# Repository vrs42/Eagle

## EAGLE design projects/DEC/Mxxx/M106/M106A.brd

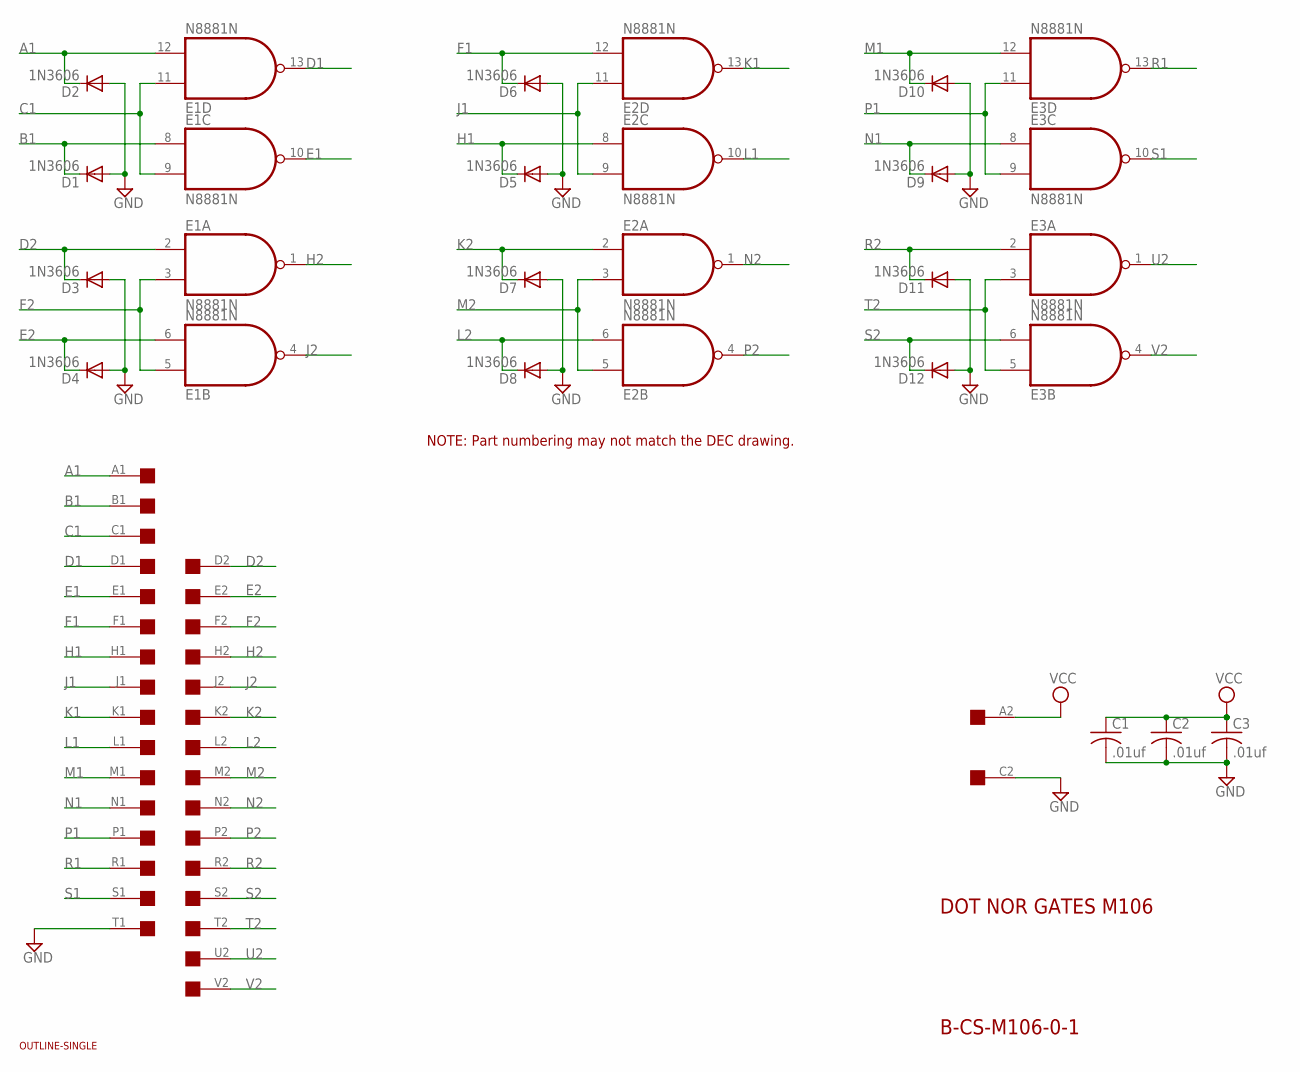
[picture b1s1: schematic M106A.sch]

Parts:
C1, C2, C3: .01uf; C050-025X075
D1, D2, D3, D4, D5, D6, D7, D8, D9, D10, D11, D12: 1N3606; DO35-10
E1, E2, E3: N8881N; DIL14
U$1: SINGLE; EDGE-CON2
U$4: OUTLINE-SINGLE; SINGLE

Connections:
A1: D2.C, E1.12 (I1), U$1.A1
B1: D1.C, E1.8 (I0), U$1.B1
C1: E1.9 (I1), E1.11 (I0), U$1.C1
D1: E1.13 (O), U$1.D1
D2: D3.C, E1.2 (I0), U$1.D2
E1: E1.10 (O), U$1.E1
E2: D4.C, E1.6 (I1), U$1.E2
F1: D6.C, E2.12 (I1), U$1.F1
F2: E1.3 (I1), E1.5 (I0), U$1.F2
GND: C1.2, C2.2, C3.2, D1.A, D2.A, D3.A, D4.A, D5.A, D6.A, D7.A, D8.A, D9.A, D10.A, D11.A, D12.A, E1.7 (GND), E2.7 (GND), E3.7 (GND), U$1.C2, U$1.T1
H1: D5.C, E2.8 (I0), U$1.H1
H2: E1.1 (O), U$1.H2
J1: E2.9 (I1), E2.11 (I0), U$1.J1
J2: E1.4 (O), U$1.J2
K1: E2.13 (O), U$1.K1
K2: D7.C, E2.2 (I0), U$1.K2
L1: E2.10 (O), U$1.L1
L2: D8.C, E2.6 (I1), U$1.L2
M1: D10.C, E3.12 (I1), U$1.M1
M2: E2.3 (I1), E2.5 (I0), U$1.M2
N1: D9.C, E3.8 (I0), U$1.N1
N2: E2.1 (O), U$1.N2
P1: E3.9 (I1), E3.11 (I0), U$1.P1
P2: E2.4 (O), U$1.P2
R1: E3.13 (O), U$1.R1
R2: D11.C, E3.2 (I0), U$1.R2
S1: E3.10 (O), U$1.S1
S2: D12.C, E3.6 (I1), U$1.S2
T2: E3.3 (I1), E3.5 (I0), U$1.T2
U2: E3.1 (O), U$1.U2
V2: E3.4 (O), U$1.V2
VCC: C1.1, C2.1, C3.1, E1.14 (VCC), E2.14 (VCC), E3.14 (VCC), U$1.A2

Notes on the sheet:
DOT NOR GATES M106
B-CS-M106-0-1
NOTE: Part numbering may not match the DEC drawing.

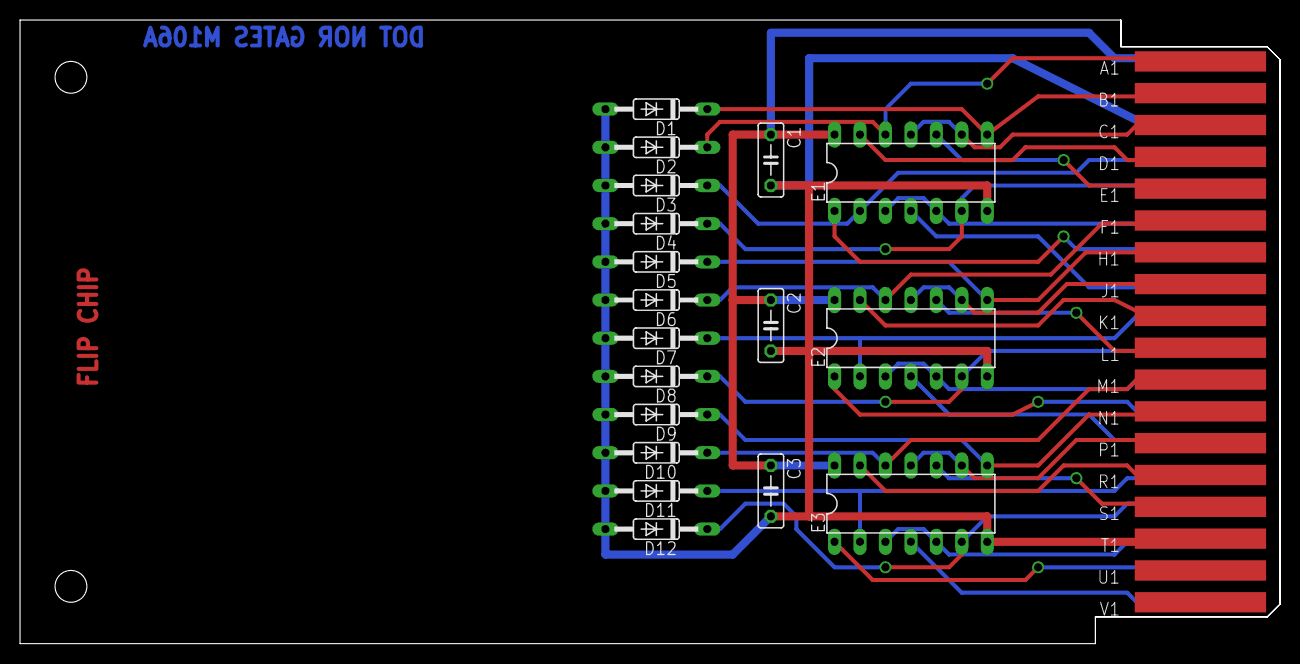
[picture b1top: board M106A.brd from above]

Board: 2 copper layers, 125.7 x 62.2 mm, 20 parts (0 on the bottom side), 32 nets.

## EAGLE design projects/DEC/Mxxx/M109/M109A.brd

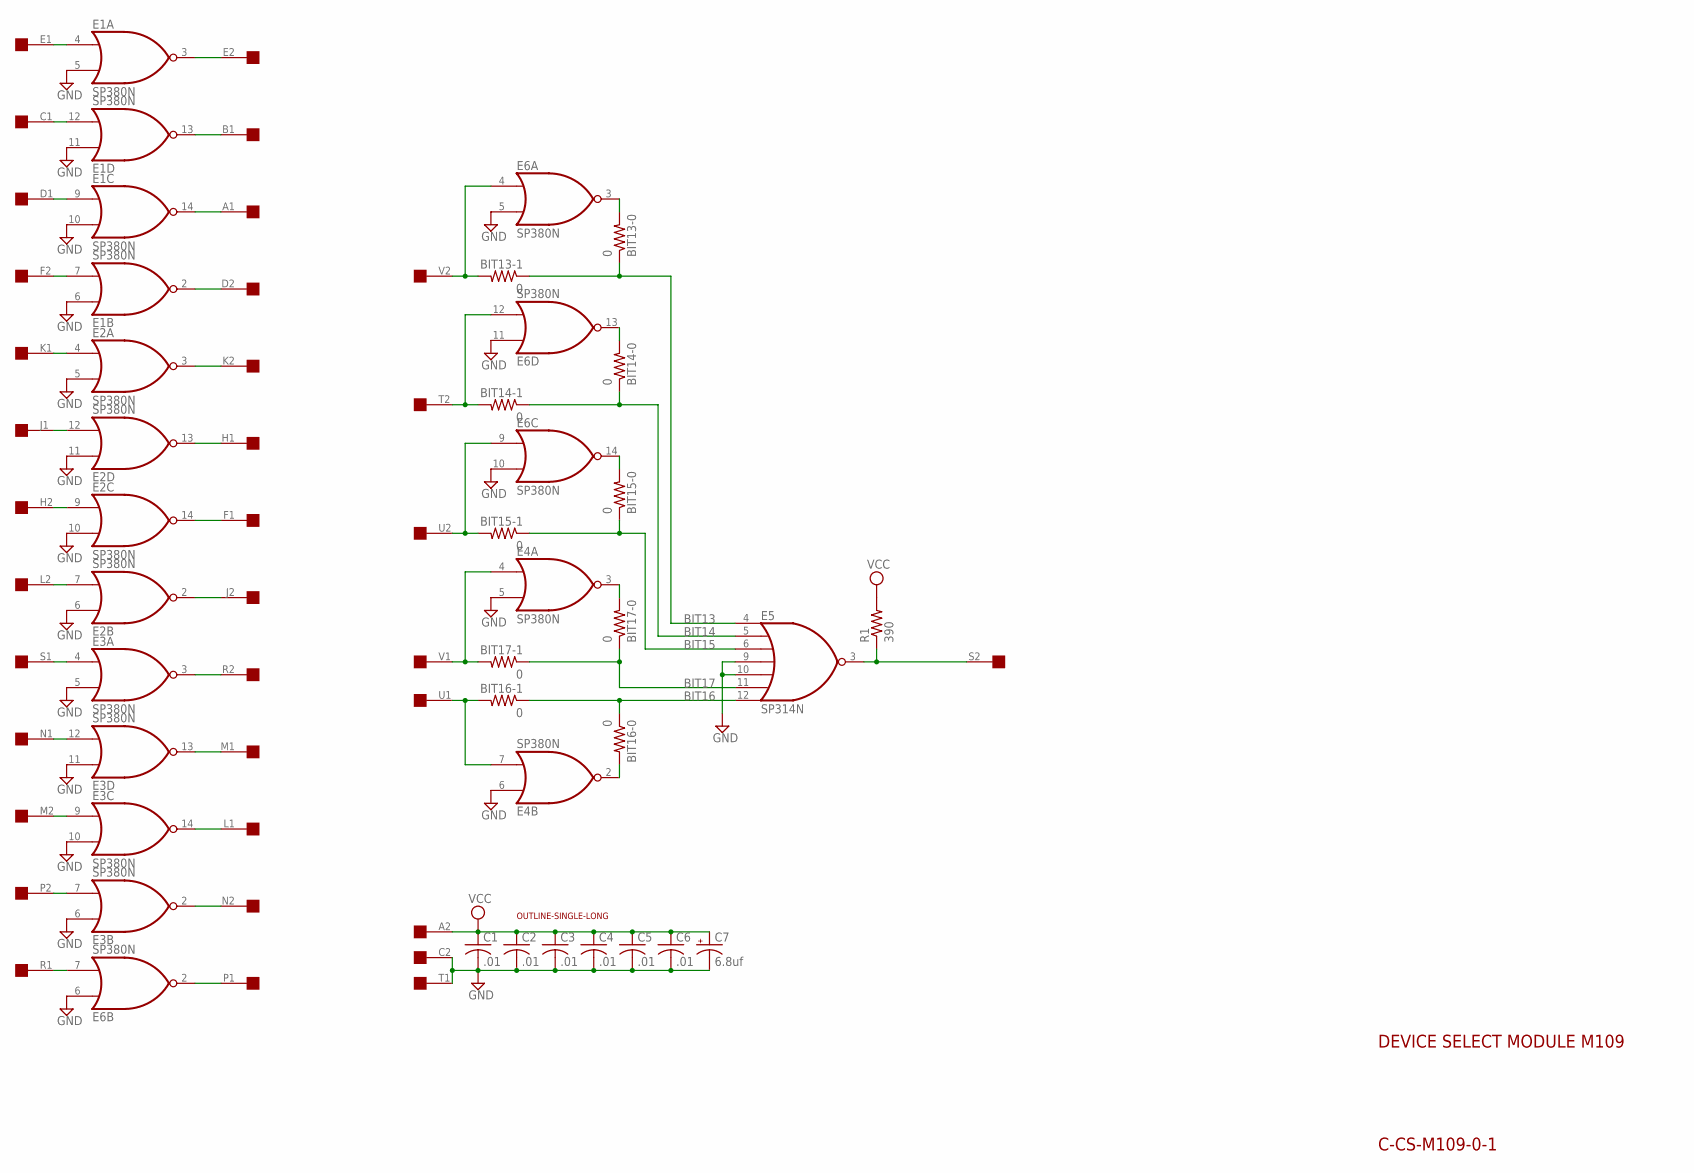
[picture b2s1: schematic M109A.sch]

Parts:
BIT13-0, BIT13-1, BIT14-0, BIT14-1, BIT15-0, BIT15-1, BIT16-0, BIT16-1, BIT17-0, BIT17-1: 0; 0207/10
C1, C2, C3, C4, C5, C6: .01; C050-025X075
C7: 6.8uf; E22-6
E1, E2, E3, E4, E6: SP380N; DIL14
E5: SP314N; DIL14
R1: 390; 0207/10
U$1: SINGLE; EDGE-CON2
U$2: OUTLINE-SINGLE-LONG; SINGLE-LONG

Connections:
BIT13: BIT13-0.1, BIT13-1.1, E5.4 (I0)
BIT14: BIT14-0.1, BIT14-1.1, E5.5 (I1)
BIT15: BIT15-0.1, BIT15-1.1, E5.6 (I2)
BIT16: BIT16-0.1, BIT16-1.1, E5.12 (I6)
BIT17: BIT17-0.1, BIT17-1.1, E5.11 (I5)
GND: C1.2, C2.2, C3.2, C4.2, C5.2, C6.2, C7.-, E1.1 (GND), E1.5 (I1), E1.6 (I0), E1.10 (I1), E1.11 (I0), E2.1 (GND), E2.5 (I1), E2.6 (I0), E2.10 (I1), E2.11 (I0), E3.1 (GND), E3.5 (I1), E3.6 (I0), E3.10 (I1), E3.11 (I0), E4.1 (GND), E4.5 (I1), E4.6 (I0), E5.1 (GND), E5.9 (I3), E5.10 (I4), E6.1 (GND), E6.5 (I1), E6.6 (I0), E6.10 (I1), E6.11 (I0), U$1.C2, U$1.T1
unnamed: E1.4 (I0), U$1.E1
unnamed: E2.12 (I1), U$1.J1
unnamed: E1.3 (O), U$1.E2
unnamed: E1.2 (O), U$1.D2
unnamed: E2.9 (I0), U$1.H2
unnamed: E2.3 (O), U$1.K2
unnamed: E2.13 (O), U$1.H1
unnamed: E3.13 (O), U$1.M1
unnamed: BIT15-0.2, E6.14 (O)
unnamed: E3.7 (I1), U$1.P2
unnamed: E6.7 (I1), U$1.R1
unnamed: E3.2 (O), U$1.N2
unnamed: BIT17-1.2, E4.4 (I0), U$1.V1
unnamed: BIT14-1.2, E6.12 (I1), U$1.T2
unnamed: BIT15-1.2, E6.9 (I0), U$1.U2
unnamed: E6.2 (O), U$1.P1
unnamed: E1.12 (I1), U$1.C1
unnamed: E1.7 (I1), U$1.F2
unnamed: E1.9 (I0), U$1.D1
unnamed: BIT14-0.2, E6.13 (O)
unnamed: BIT17-0.2, E4.3 (O)
unnamed: E1.14 (O), U$1.A1
unnamed: E1.13 (O), U$1.B1
unnamed: E2.14 (O), U$1.F1
unnamed: E2.2 (O), U$1.J2
unnamed: E2.7 (I1), U$1.L2
unnamed: E2.4 (I0), U$1.K1
unnamed: E3.14 (O), U$1.L1
unnamed: E3.12 (I1), U$1.N1
unnamed: E3.9 (I0), U$1.M2
unnamed: BIT16-1.2, E4.7 (I1), U$1.U1
unnamed: E3.3 (O), U$1.R2
unnamed: BIT16-0.2, E4.2 (O)
unnamed: BIT13-1.2, E6.4 (I0), U$1.V2
unnamed: BIT13-0.2, E6.3 (O)
unnamed: E5.3 (O), R1.1, U$1.S2
unnamed: E3.4 (I0), U$1.S1
VCC: C1.1, C2.1, C3.1, C4.1, C5.1, C6.1, C7.+, E1.8 (VCC), E2.8 (VCC), E3.8 (VCC), E4.8 (VCC), E5.8 (VCC), E6.8 (VCC), R1.2, U$1.A2

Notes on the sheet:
DEVICE SELECT MODULE M109
C-CS-M109-0-1

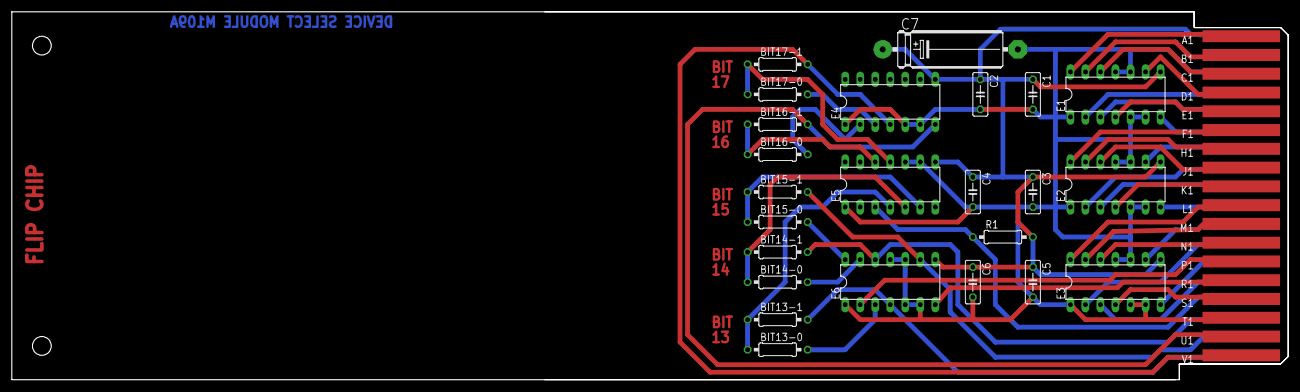
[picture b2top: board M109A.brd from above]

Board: 2 copper layers, 215.9 x 62.2 mm, 27 parts (0 on the bottom side), 44 nets.

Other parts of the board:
U$3: FLIPCHIP

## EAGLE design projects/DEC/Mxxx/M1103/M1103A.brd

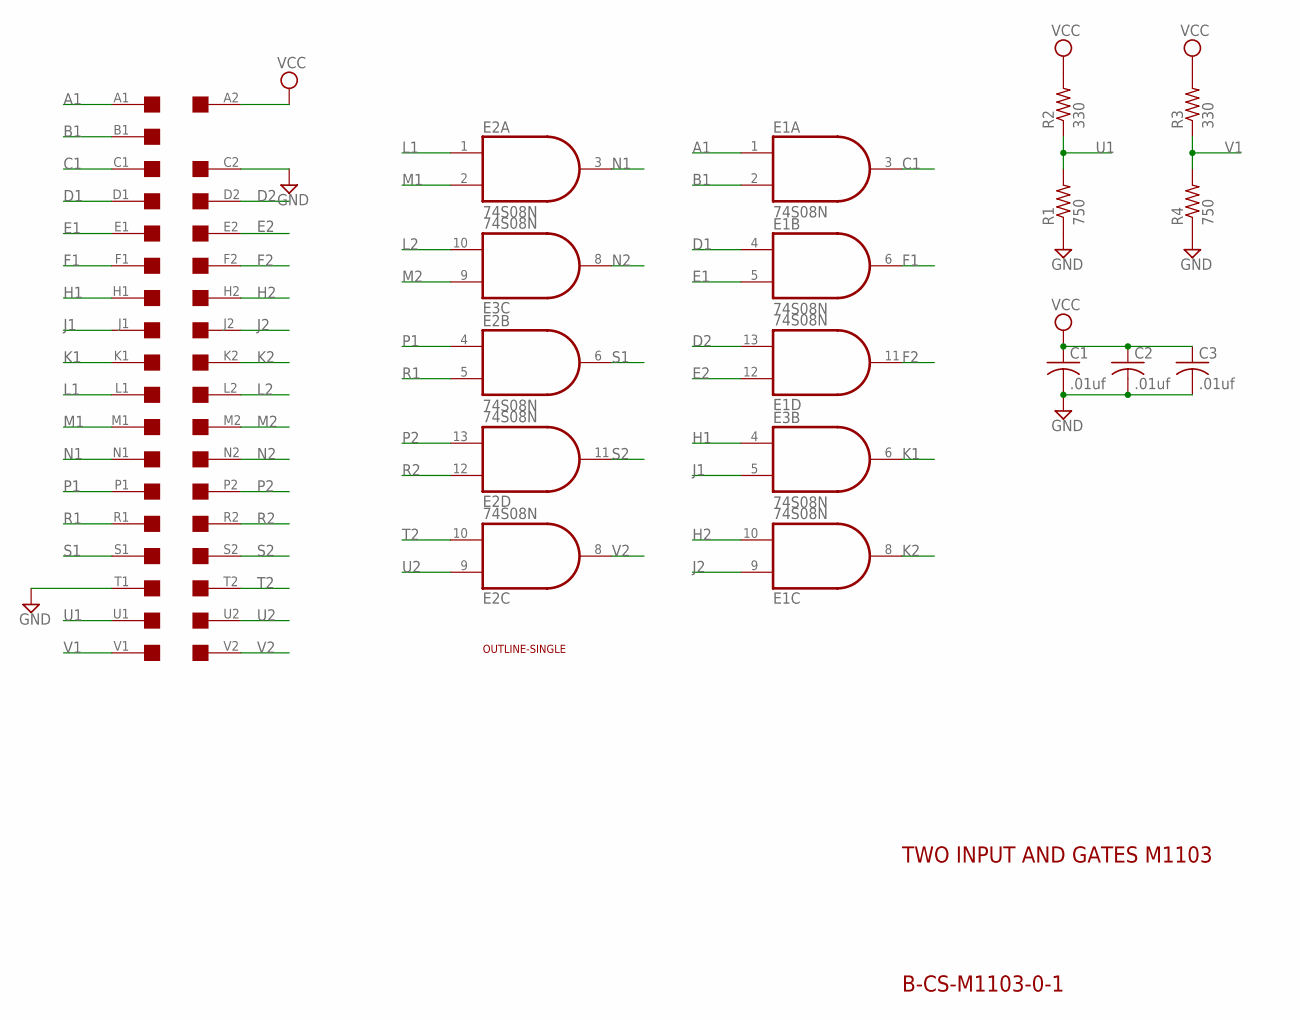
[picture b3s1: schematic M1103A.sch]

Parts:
C1, C2, C3: .01uf; C050-025X075
E1, E2, E3: 74S08N; DIL14
R1, R4: 750; 0207/10
R2, R3: 330; 0207/10
U$1: SINGLE; EDGE-CON2
U$2: OUTLINE-SINGLE; SINGLE

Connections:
A1: E1.1 (I0), U$1.A1
B1: E1.2 (I1), U$1.B1
C1: E1.3 (O), U$1.C1
D1: E1.4 (I0), U$1.D1
D2: E1.13 (I1), U$1.D2
E1: E1.5 (I1), U$1.E1
E2: E1.12 (I0), U$1.E2
F1: E1.6 (O), U$1.F1
F2: E1.11 (O), U$1.F2
GND: C1.2, C2.2, C3.2, E1.7 (GND), E2.7 (GND), E3.7 (GND), R1.1, R4.1, U$1.C2, U$1.T1
H1: E3.4 (I0), U$1.H1
H2: E1.10 (I1), U$1.H2
J1: E3.5 (I1), U$1.J1
J2: E1.9 (I0), U$1.J2
K1: E3.6 (O), U$1.K1
K2: E1.8 (O), U$1.K2
L1: E2.1 (I0), U$1.L1
L2: E3.10 (I1), U$1.L2
M1: E2.2 (I1), U$1.M1
M2: E3.9 (I0), U$1.M2
N1: E2.3 (O), U$1.N1
N2: E3.8 (O), U$1.N2
P1: E2.4 (I0), U$1.P1
P2: E2.13 (I1), U$1.P2
R1: E2.5 (I1), U$1.R1
R2: E2.12 (I0), U$1.R2
S1: E2.6 (O), U$1.S1
S2: E2.11 (O), U$1.S2
T2: E2.10 (I1), U$1.T2
U1: R1.2, R2.1, U$1.U1
U2: E2.9 (I0), U$1.U2
V1: R3.1, R4.2, U$1.V1
V2: E2.8 (O), U$1.V2
VCC: C1.1, C2.1, C3.1, E1.14 (VCC), E2.14 (VCC), E3.14 (VCC), R2.2, R3.2, U$1.A2

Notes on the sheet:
TWO INPUT AND GATES M1103
B-CS-M1103-0-1

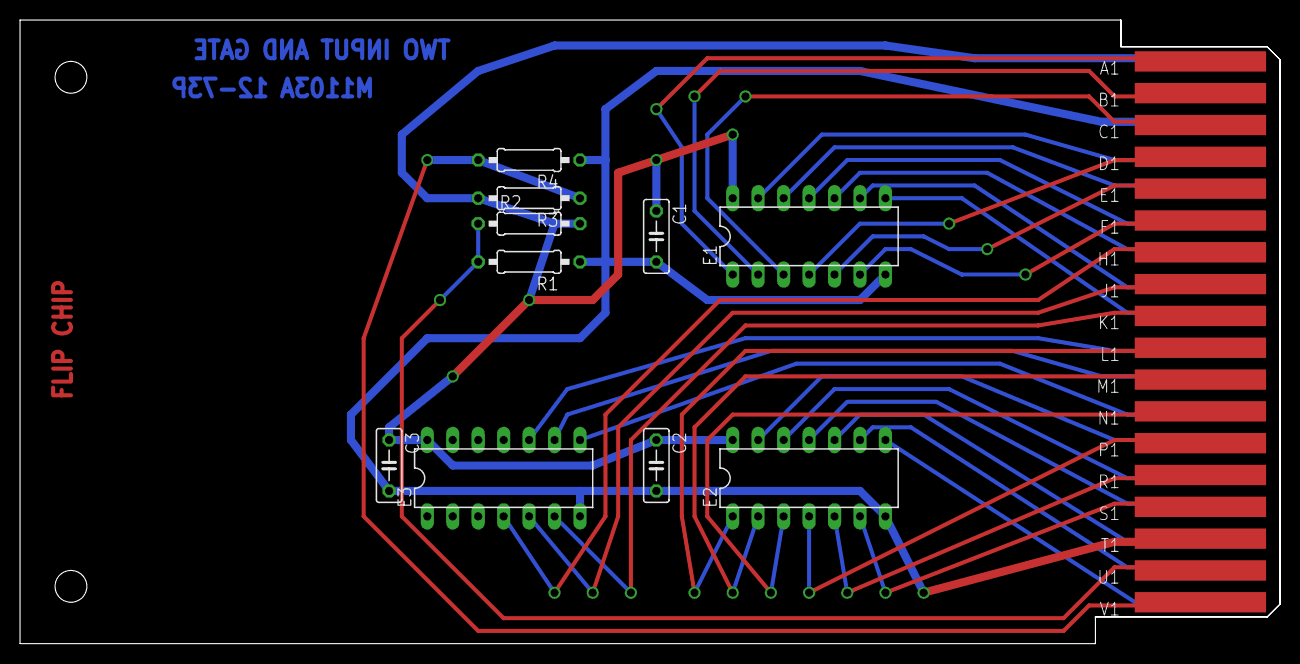
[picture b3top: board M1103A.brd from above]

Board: 2 copper layers, 125.7 x 62.2 mm, 12 parts (0 on the bottom side), 34 nets.

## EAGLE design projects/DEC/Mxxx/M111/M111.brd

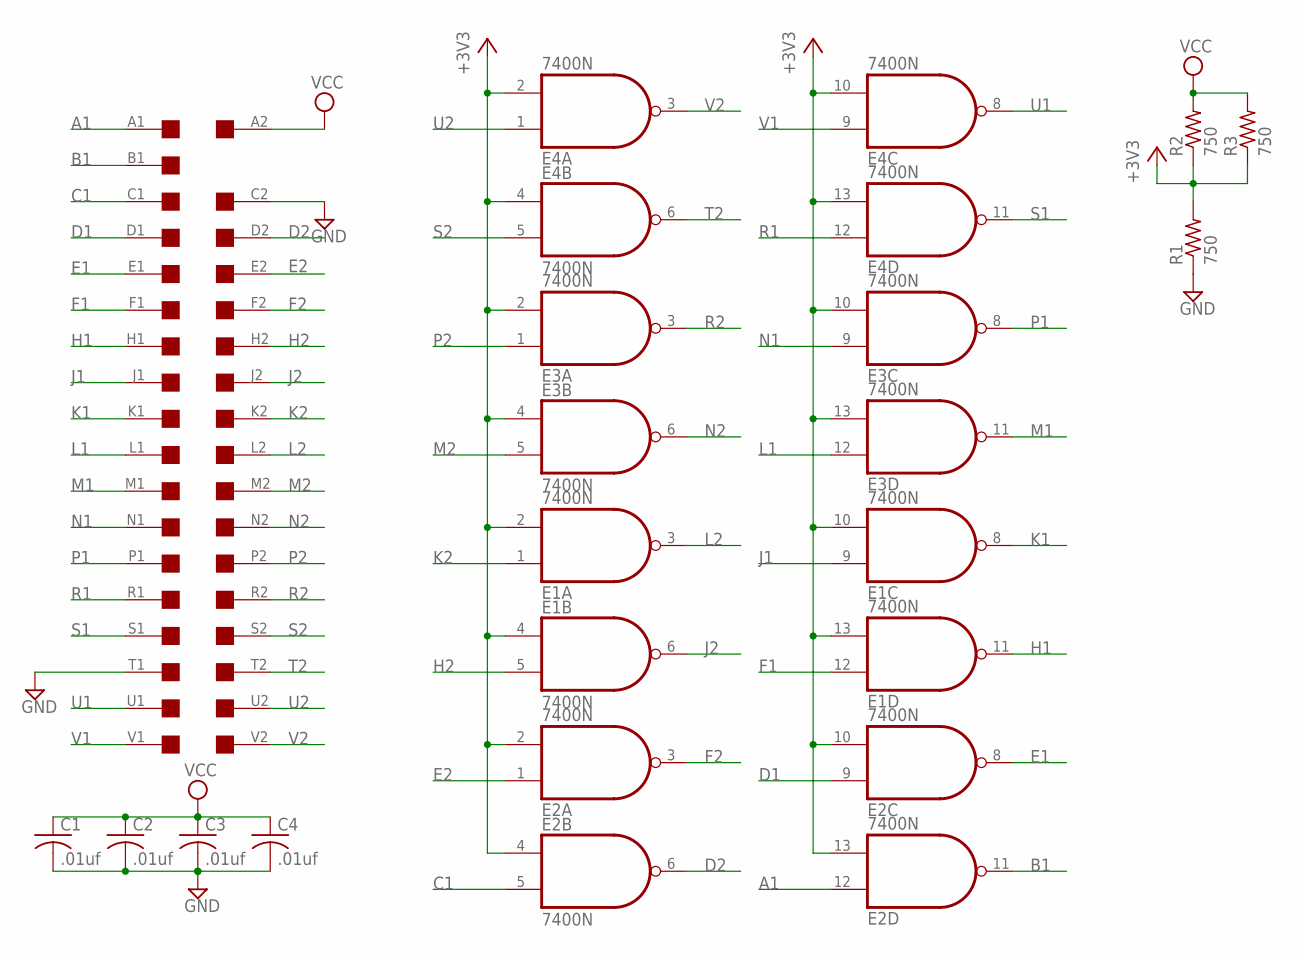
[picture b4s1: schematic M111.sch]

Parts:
A: EDGE-2CONNECTOR; EDGE-CON2
C1, C2, C3, C4: .01uf; C050-025X075
E1, E2, E3, E4: 7400N; DIL14
R1, R2, R3: 750; 0207/10

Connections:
+3V3: E1.2 (I1), E1.4 (I0), E1.10 (I1), E1.13 (I1), E2.2 (I1), E2.4 (I0), E2.10 (I1), E2.13 (I1), E3.2 (I1), E3.4 (I0), E3.10 (I1), E3.13 (I1), E4.2 (I1), E4.4 (I0), E4.10 (I1), E4.13 (I1), R1.2, R2.1, R3.1
A1: A.A1, E2.12 (I0)
B1: A.B1, E2.11 (O)
C1: A.C1, E2.5 (I1)
D1: A.D1, E2.9 (I0)
D2: A.D2, E2.6 (O)
E1: A.E1, E2.8 (O)
E2: A.E2, E2.1 (I0)
F1: A.F1, E1.12 (I0)
F2: A.F2, E2.3 (O)
GND: A.C2, A.T1, C1.2, C2.2, C3.2, C4.2, E1.7 (GND), E2.7 (GND), E3.7 (GND), E4.7 (GND), R1.1
H1: A.H1, E1.11 (O)
H2: A.H2, E1.5 (I1)
J1: A.J1, E1.9 (I0)
J2: A.J2, E1.6 (O)
K1: A.K1, E1.8 (O)
K2: A.K2, E1.1 (I0)
L1: A.L1, E3.12 (I0)
L2: A.L2, E1.3 (O)
M1: A.M1, E3.11 (O)
M2: A.M2, E3.5 (I1)
N1: A.N1, E3.9 (I0)
N2: A.N2, E3.6 (O)
P1: A.P1, E3.8 (O)
P2: A.P2, E3.1 (I0)
R1: A.R1, E4.12 (I0)
R2: A.R2, E3.3 (O)
S1: A.S1, E4.11 (O)
S2: A.S2, E4.5 (I1)
T2: A.T2, E4.6 (O)
U1: A.U1, E4.8 (O)
U2: A.U2, E4.1 (I0)
V1: A.V1, E4.9 (I0)
V2: A.V2, E4.3 (O)
VCC: A.A2, C1.1, C2.1, C3.1, C4.1, E1.14 (VCC), E2.14 (VCC), E3.14 (VCC), E4.14 (VCC), R2.2, R3.2

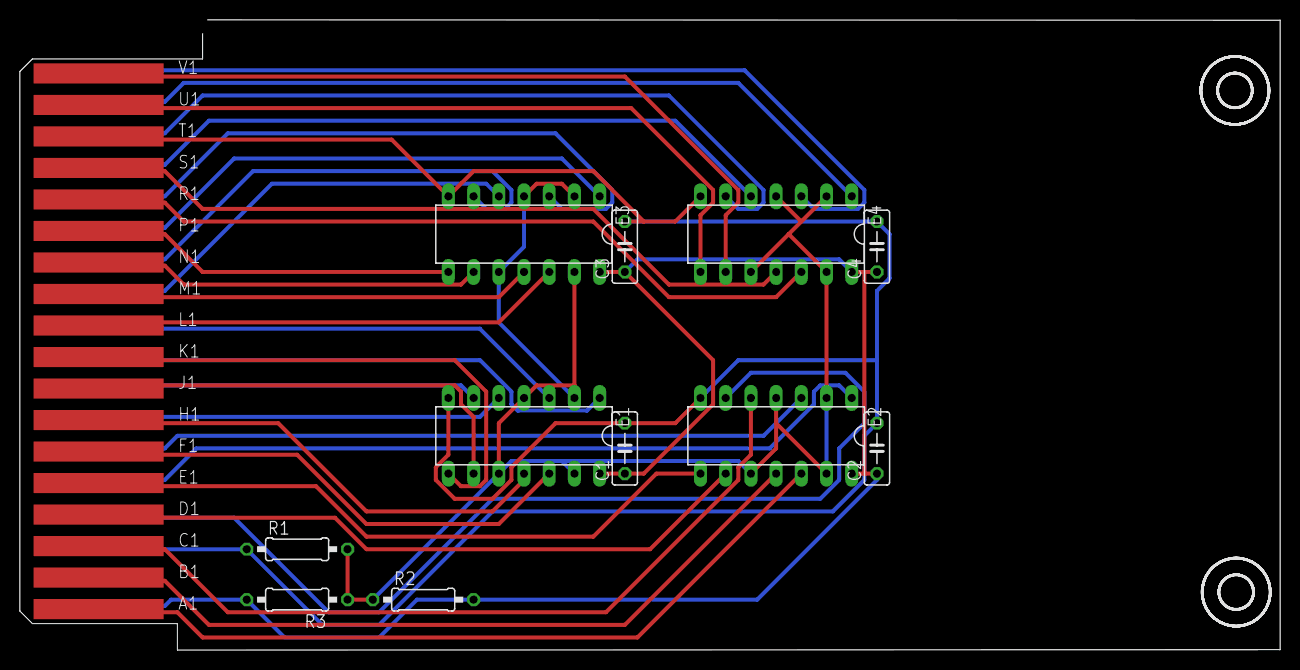
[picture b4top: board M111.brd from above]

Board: 2 copper layers, 127.0 x 63.5 mm, 14 parts (0 on the bottom side), 35 nets.

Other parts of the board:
U$2, U$3: 3,3
